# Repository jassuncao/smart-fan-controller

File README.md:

# smart-fan-controller
Device to control a bathroom fan offering two modes of operation: level of humidity or timed mode

# Introduction

## A bit of story.
This project originated from a request of my girlfriend. She needed a bathroom fan for her new house but she wanted to avoid the ones that run every time the light is turned on. 
We looked for fans with timer or humidity sensors in our local stores, but all them were big for the existing hole. The ones that fitted, were the basic ones we were trying to avoid. 

I decided for one of the basic ones, and then noticed it had a small compartment with a plastic cover. 
The cover featured a small window, suggesting it was designed for a sensor. 
This gave me the idea of making a fan controller that could fit inside the compartment, and make use of the small window for a humidity sensor.

[INSERT PHOTO OF THE FAN]

## Requirements

The initial requirements for the fan controller were the following:
* Fit inside the compartment provided by the fan.
* Feature a humidity sensor to activate the fan depending on the level of humidity.
* Low power consumption.
* Adjustable humidity threshold.

The ability to set the humidity threshold triggered a new requirement
I spent some time thinking of ways that could be used to set the humidity threshold when the idea of using the light of the bathroom come to my mind. 
This way there wouldn't be no need to use a ladder to fiddle with the fan or the need for a remote control.
After analyzing various options, I decided to use the following scheme to configure the humidity threshold.
* The user toggles the light switch a specific number of times.
* The device enter configuration mode.
* The user toggle the switch a number of times equivalent to the desired humidity threshold. For example, five times for a 50% humidity.
* After a period without light pulses the device leaves configuration mode

# The hardware

The hardware can be divided in the following major blocks:
* Power supply
* Humidity sensor module
* Light sensor
* Motor control
* Zero cross detection
* Microcontroller

The power supply reduces the mains voltage (220V AC) to a suitable voltage for use by the microcontroller and the humidity sensor module.

The humidity sensor module has built in all the electronics needed for relative humidity acquisition. This includes the actual humidity sensor element, temperature sensor, and interface logic. The module provides a one wire interface used for humidity and temperature readings.

A light-dependent resistor (LDR) is used as light sensor and feeds one ADC input of the microcontroller.

The fan motor is driven using a TRIAC. A TRIAC is a cheaper and smaller alternative to a relay, another common device used to drive AC loads.

Zero cross detection is used for triggering the TRIAC and as a time source.

[Block diagram]

## The microcontroller

This project uses Atmel's ATtiny13 microcontroller. The reasons behind this choice were physical size and availability in my home lab.
The ATtiny13 microcontroller, can run at up to 20 MHz and features 1 KByte of flash and six I/O pins in an eight pin package. 
The number of of I/O pins exceeds the requirements and leaves us with two spare pins. One of these spare pins is used to drive a feedback LED introduced later on.

## Power supply
The power for the microcontroller and sensors is provided by a transform-less power supply.
A voltage divider with a zener is used to reduce the mains voltage to approximately 5V. This provides a relatively stable output as long as the as the output load is kept below the zener current.

The voltage divider uses a dropper capacitor and a resistor as input impedance. The dropper capacitor provides most of the input impedance and the resistor limits the inrush current. If the input impedance was purely resistive we would have considerable losses as heat, a side effect less noticeable with this arrangement.
One disadvantage is that we need to use a capacitor with high capacitance and a high voltage rating. Capacitors with these two characteristics are not small and space is not a commodity in abundance in the fan enclosure.

Rectification is performed with a single diode, meaning we get half wave rectification. This is less efficient in terms of output current but allows direct driving of the triac, making the use of a optocoupler or optotriac unnecessary.
If a full wave rectifier was used, the microcontroller and the triac would not share a common reference. With the full wave rectifier, the microcontroller's ground would be provided by 
two diodes, with one conducting to neutral in one half cycle and the other conducting to live in the other half cycle. In this situation we would only be able to drive the triac in half of the cycles.
Finally two electrolytic capacitors are used to reduce ripple and stabilize the output voltage.

The values for the capacitor and the resistor were obtained using a spreadsheet provided by Designer Circuits LLC. This spreadsheet is a companion to the excelent design note "Transformerless Power Supply Design". Microchip Application Note AN954 was used initially but the equations presented in that document were not clear and the results from simulation didn't match the calculations. 

## Triac control 

Ideally,triacs should be triggered when the current is at its lowest value. For pure resistive loads, where the current is in phase with the voltage, the triac should be triggered when the voltage crosses zero.
In the case of a fan motor, or any other kind of device that involves coils, we have an inductive load. 
These kinds of loads introduce a phase shift in the current relative to the voltage. For practical purposes, the instant where current is zero will be delayed relatively to the instant the voltage is zero. This means that for inductive loads, instead of zero voltage detection we should use zero current detection.

A possible approach to zero current detection is the use of a shunt resistor and a operational amplifier to measure the current. This approach not only introduces a new IC with specific power requirements, but also additional components. Since PCB real estate is not abundant, the approach was discarded.
Another approach suggested in a NXP application note (AN467) is to monitor the triac gate voltage with respect to the T1 terminal. This can be achieved with a few resistors and a window comparator. Some microcontrollers include a window comparator, but that is not the case for the ATtiny13. Adding an external window comparator IC was also discarded due to space restrictions.

Exhausted the possibilities, I decided to use zero voltage crossing and hope the EMI noise and power losses would be minimal.

To reduce the power needed to trigger the triac a simple trick is used. Instead of driving the gate continuously, the gate is driven with a pulse train. With this we can achieve a reduction of the power required to driver the triac.

After some failed experiments with other types of triacs, I ended using the BTA204-800E. This triac is part of NXP 3Q Hi-Com Triac family and offers the following benefits:

* 3Q technology for improved noise immunity
* Direct triggering from low power drivers and logic ICs
* High blocking voltage capability
* High commutation capability
* Planar passivated for voltage ruggedness and reliability
* Sensitive gate for easy logic level triggering
* Triggering in three quadrants only

Thanks to this characteristics is possible to drive the triac directly with a microcontroller pin. 
It also eliminates the need for a snubber network. A snubber network reduces the side effects produced when driving inductive loads. It is made of a RC circuit in parallel with the load. 
Due to the size of a capacitor rated for 220V AC, it would be quite difficult to fit all inside.

One disadvantage of this Triac is that it can only be triggered in three quadrants. The 3+ quadrant (T2-, G+) can't be used, meaning we can't drive the gate with a circuit that sources current. Instead we need a circuit that sinks current. In practical terms, we can see the triac gate as a active low pin. This is not an issue because most digital output pins can sink more current that they can source current.

[Include figure from NXP three-quadrant_NXP Hi-Com triacs]

As mentioned before, other triacs were tested before the BTA204-800E was chosen. They worked fine during tests with 20V AC and a incandescent lamp as a load, but not so fine when using the actual fan. I experienced unstable behavior or a completely inability to rotate the fan, that I assume was caused by noise due to lack of a snubber network.

## Sensors

Two sensors are used. A humidity sensor module and a light dependent resistor (LDR).

For the humidity sensor is used the ubiquitous DHT11. This module has limited precision (+/-5%) and limited range (from 20% to 80%). These characteristics are enough for the requirements of a bathroom fan. If more precision is needed, replacing the DHT11 with is bigger brother DHT22, can be an option.
This module features a non-standard one wire interface used by the microcontroller to acquire humidity and temperature readings. 

A voltage divider made of a LDR and a fixed resistor provides a voltage that varies accordingly to the amount of light. This voltage is feed into a analog input of the microcontroller and converted into a digital value.

## Zero cross detection

# Software
* Zero cross detection
* Triac firing

* "User interface" 

## Sensors

### DHT111

The code used to read humidity values is based on a open source library developed by Angus Gratton (original source: https://github.com/projectgus/flatdrier).
Some minor changes were made to reduce the size of the compiled code. For example, the number of invocations of external functions was reduced, some portions of the code have been reorganized, and a few simplifications were used to make the job of the compiler easier.

When the compiler translates a C function invocation, the resulting assembly code is composed of three sections. The function prologue, the call of the routine implementing the function, and a function epilogue. Of these, the function prologue is the one that usually uses more instructions, with an amount depending on the number of arguments. By reducing the number of invocations we can save a few precious bytes. This was done in the function used to read bits sent by the DHT11. 

The original library uses the following portion of code to store the bits sent by the DHT11:

	...
	for(int8_t bit = 7; bit >= 0; bit--) {
	  if(!listen_edge(false, 20, 80)) // 50us bit prelude
		return bad_bit_prelude;
	  uint8_t bit_length = listen_edge(true, 10, 90); // bit signal - 26-28us for 0 70us for 1
	  if(!bit_length)
		return bad_bit_data_pause; // invalid data pulse
	  if(bit_length > 30)
		raw.bytes[byte] |= _BV(bit);
	}
	...

And this is the new code used for the same purpose.
	...
	uint8_t aux = 0;	
	for(uint8_t bit = 0; bit < 8; bit++) {
		int8_t b = read_bit();
		if(b < 0){
			return bad_bit_data_pause; // invalid data pulse
		}
		
		aux = aux << 1;
		aux |= b & 0x01;
	}
	raw.bytes[byte] = aux;
	...

The number of if statements inside the for loop have been reduced to one. This eliminates a couple of instructions used to test and branch.

By using an auxiliary variable we reduced the overhead of accessing the `raw.bytes` array. In the original code, a few additional instructions are needed to fetch the contents of the array position from RAM into a register. In the new code this is not needed. The compiler translates the auxiliary variable into a register that is used directly during logic operations. After the for finishes, the contents of this register is stored into RAM.
	
* Size optimizations

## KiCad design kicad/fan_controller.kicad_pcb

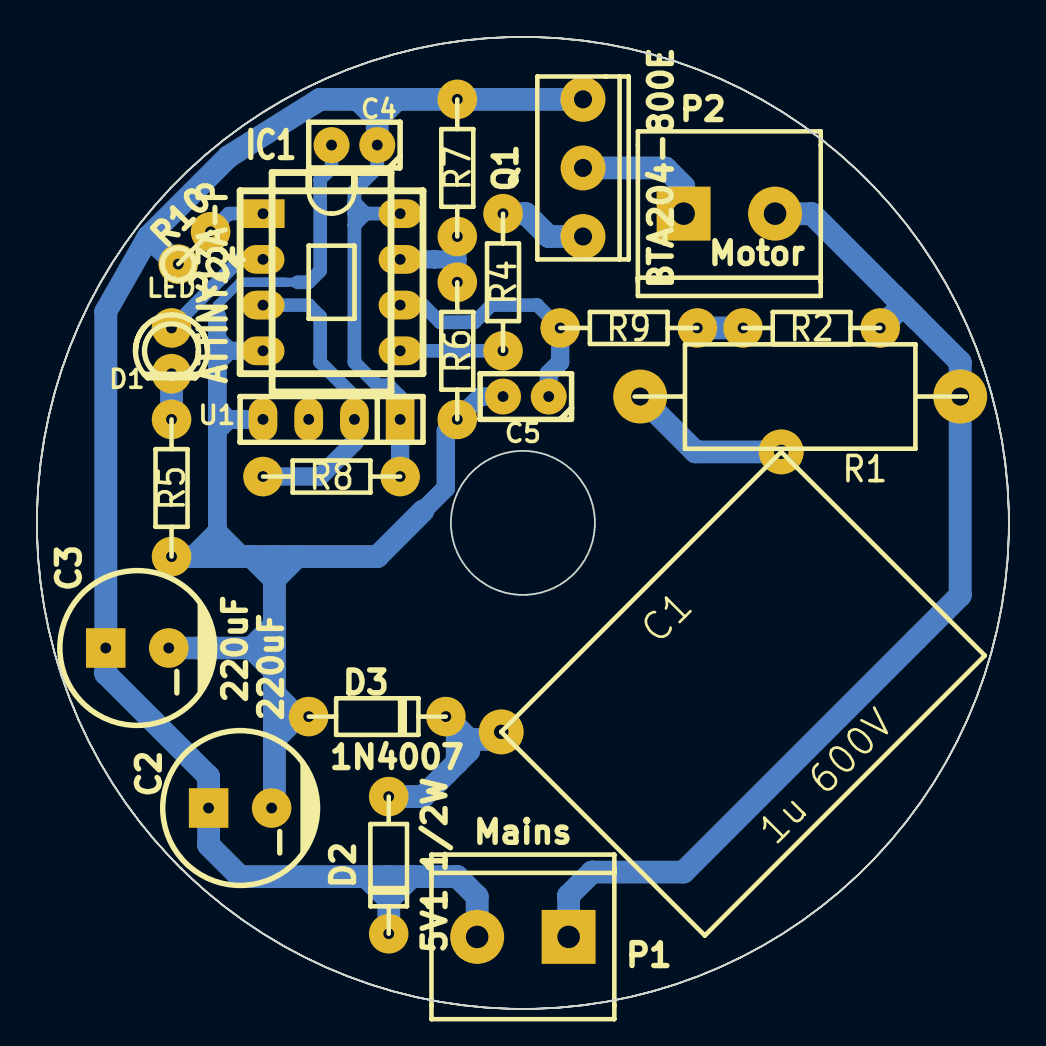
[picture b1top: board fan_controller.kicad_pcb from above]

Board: 2 copper layers, 54.0 x 54.0 mm, 22 parts (0 on the bottom side), 15 nets.

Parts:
C1: 1u 600V; cnp_22x16_horz
C2, C3: 220uF; CP_8x11.5mm
C4: 100nF; cnp_3mm_disc
C5: 100pF; cnp_3mm_disc
D1: LED; led_3mm_red
D2: 5V1 1/2W; diode_do35
D3: 1N4007; diode_do35
IC1: ATTINY13A-P; dil_8-300_socket
P1: Mains; mors_2p
P2: Motor; mors_2p
Q1: BTA204-800E; to220
R1: 120R 2W; R12x5.2
R2, R9: 510K; RC03
R4: 330R; RC03
R5: 2K2; RC03
R6: LDR; RC03
R7, R8: 10K; RC03
R10: 20k; rc03_vert
U1: DHT11; pin_strip_4

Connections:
+5V: C2.1, C3.1, C4.1, D2.2, IC1.8, P1.2, Q1.3, R7.1, R8.1, R10.1, U1.1
/L: P1.1, P2.2, R1.1, R2.1
GND: C2.2, C3.2, C4.2, C5.2, D3.1, IC1.4, R5.2, R6.2, U1.4
unnamed: C1.1, R1.2
unnamed: C1.2, D2.1, D3.2
unnamed: C5.1, IC1.6, R9.2
unnamed: D1.1, IC1.2
unnamed: D1.2, R5.1
unnamed: IC1.1, R10.2
unnamed: IC1.3, R8.2, U1.2
unnamed: IC1.5, R4.2
unnamed: IC1.7, R6.1, R7.2
unnamed: P2.1, Q1.2
unnamed: Q1.1, R4.1
unnamed: R2.2, R9.1

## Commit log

2016-02-04 * Initial import
2016-02-05 * Inverts the triac signal. Uses low (G-) so that we operate in T2+ G- and T- G-. The triac in use BTA204-800E only supports three quadrants but uses less gate current and is snubber less
2016-02-21 * The DHT11 driver doesn't use software delays anymore but instead polls the data line until the desired signal is found or until a timeout occurs. * Include code to read the LDR
2016-02-27 * Working in "setup" mode and trying to use the 50Hz as the source for a clock.
2016-03-12 * Saving configuration to flash * Using 50hz for timing purposes
2016-03-20 * Fixes some issues and removes some test code from main.c to tests.c
2016-04-06 * Improvements to reduce binary size
2016-04-17 * Adds a more robust debounce for the zero cross detection.
2016-08-21 * Working (kinda)
2016-12-01 Working prototype
2016-12-01 * Adds more comments. * Adds an "alive" pulse every second (untested)
2016-12-04 * Adds a heartbeat indication every 5 seconds * Increases the light level threshold needed for * Limits the number of pulses in configuration mode to 11. No need to count more than 11 because every v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
2016-12-04 Adds the kicad project, simulation resources and some auxiliary documentation (datasheets and application notes)
